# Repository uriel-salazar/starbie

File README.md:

# Building cattie :)

I decided to go for the starbie idea because tI don't have any idea of how to do other PCB's or things 
But i think the idea is really cool!!

I've downloaded kicad and at first, it was a bit confusing because I didn't know how to initiliaze another library and also I didn't know
 how to label the components, but you can do it with L keyboard shorcut. 

Then, after i had everything in the right place, I update my PCB to schematic and the result was this!

After that I organize the hardware to the size of my figure I wanted to do for my PCB. I decided to go for a cat, because I really 
wanted to make something related to them. This is because I've always loved cats and it'll be fun to combine cats and coding!.

I routed the PCB and now it looked like this, I also added some tiny images to make it mine!

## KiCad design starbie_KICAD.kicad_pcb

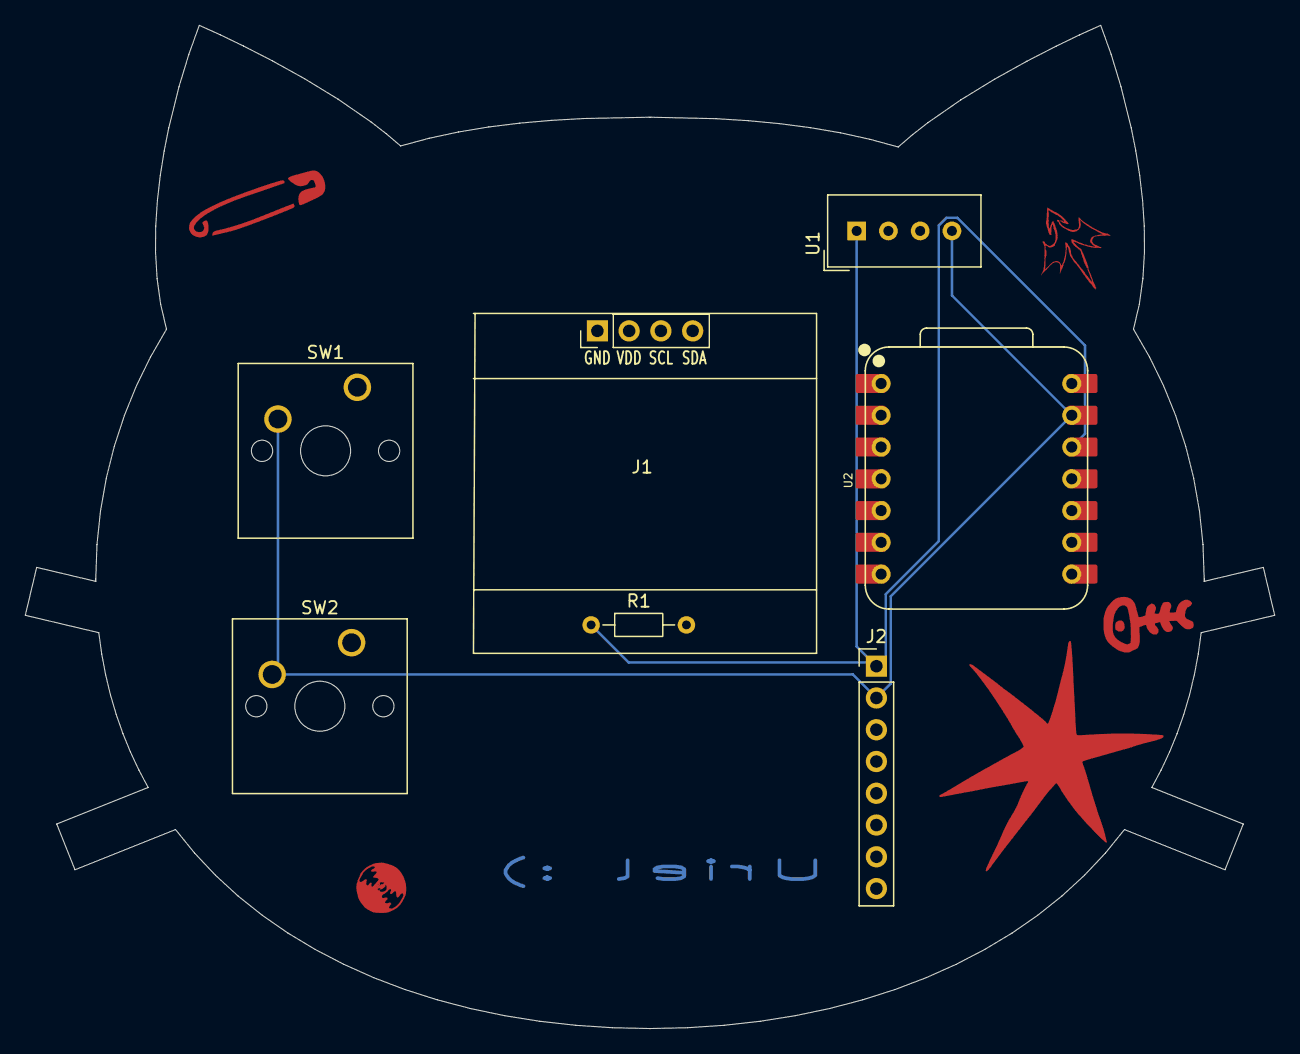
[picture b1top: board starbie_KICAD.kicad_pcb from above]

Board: 2 copper layers, 99.9 x 80.2 mm, 7 parts (0 on the bottom side), 2 nets.

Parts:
J1: Conn_01x04_Pin; Display_128x64_096_I2C
J2: Conn_01x08_Pin; PinHeader_1x08_P2.54mm_Vertical
R1: 10k; R_Axial_DIN0204_L3.6mm_D1.6mm_P7.62mm_Horizontal
SW1, SW2: SW_Push; SW_Cherry_MX_1.00u_PCB
U1: DHT11; Aosong_DHT11_5.5x12.0_P2.54mm
U2: XIAO-ESP32-C3-SMD; XIAO-ESP32-C6-DIP

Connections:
+3.3V: J2.1, R1.1, U1.1 (VDD), U2.12 (3V3_OUT)
GND: J2.2, SW1.2 (2_2), SW2.2 (2_2), U1.4 (GND), U2.13 (GND)
